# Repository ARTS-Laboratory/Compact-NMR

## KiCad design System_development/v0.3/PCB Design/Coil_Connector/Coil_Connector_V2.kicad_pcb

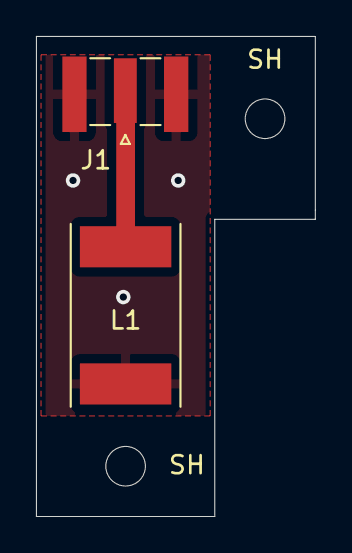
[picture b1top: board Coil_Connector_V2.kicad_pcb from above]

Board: 2 copper layers, 15.5 x 26.7 mm, 4 parts (0 on the bottom side), 2 nets.

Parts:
J1: Conn_Coaxial; SMA_Samtec_SMA-J-P-X-ST-EM1_EdgeMount
L1: L; L_Coil
SH: MountingHole_2.2mm_M2
SH#2: MountingHole_2.2mm_M2

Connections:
GND: J1.2, L1.2
unnamed: J1.1, L1.1

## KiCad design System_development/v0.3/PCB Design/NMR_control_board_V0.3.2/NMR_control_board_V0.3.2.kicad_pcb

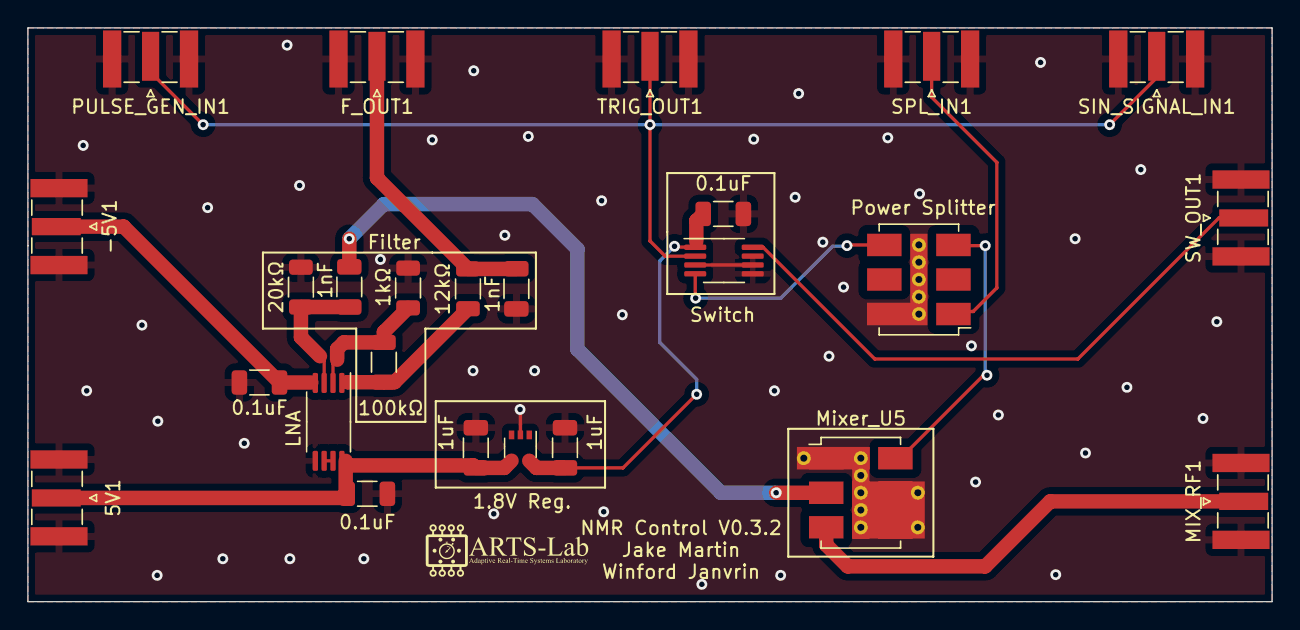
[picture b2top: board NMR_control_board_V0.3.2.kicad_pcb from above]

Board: 2 copper layers, 91.4 x 42.2 mm, 25 parts (0 on the bottom side), 16 nets.

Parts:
1.8V Reg.: NCP715-1.8V; SOT-353_SC-70-5
1kΩ, 12kΩ, 20kΩ, 100kΩ: R; R_1206_3216Metric
1nF, 1nF#2: C; C_1206_3216Metric
5V1: Conn_Coaxial; SMA_Samtec_SMA-J-P-X-ST-EM1_EdgeMount
-5V1: Conn_Coaxial; SMA_Samtec_SMA-J-P-X-ST-EM1_EdgeMount
C2, C4: 1uF; C_1206_3216Metric
C5, C6, C7: 0.1uF; C_1206_3216Metric
F_OUT1: Conn_Coaxial; SMA_Samtec_SMA-J-P-X-ST-EM1_EdgeMount
LNA: LM4565; TSSOP-8_4.4x3mm_P0.65mm
MIX_RF1: Conn_Coaxial; SMA_Samtec_SMA-J-P-X-ST-EM1_EdgeMount
Mixer_U5: ADE-6; Mini-Circuits_CD542_LandPatternPL-052
PULSE_GEN_IN1: Conn_Coaxial; SMA_Samtec_SMA-J-P-X-ST-EM1_EdgeMount
Power Splitter: ADP-2-1W; Mini-Circuits_CD636_LandPatternPL-035
SIN_SIGNAL_IN1: Conn_Coaxial; SMA_Samtec_SMA-J-P-X-ST-EM1_EdgeMount
SPL_IN1: Conn_Coaxial; SMA_Samtec_SMA-J-P-X-ST-EM1_EdgeMount
SW_OUT1: Conn_Coaxial; SMA_Samtec_SMA-J-P-X-ST-EM1_EdgeMount
Switch: ADG901BRMZ; MSOP-8_3x3mm_P0.65mm
TRIG_OUT1: Conn_Coaxial; SMA_Samtec_SMA-J-P-X-ST-EM1_EdgeMount

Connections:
GND: 1.8V Reg..2 (GND), 1kΩ.1, 1nF#2.1, 5V1.2 (Ext), 20kΩ.2, -5V1.2 (Ext), C2.2, C4.2, C5.1, C6.1, C7.1, F_OUT1.2 (Ext), LNA.5 (+IN2), MIX_RF1.2 (Ext), Mixer_U5.1 (GND), Mixer_U5.4 (GND), Mixer_U5.5 (GND), PULSE_GEN_IN1.2 (Ext), Power Splitter.6 (GND), SIN_SIGNAL_IN1.2 (Ext), SPL_IN1.2 (Ext), SW_OUT1.2 (Ext), Switch.3 (GND), Switch.5 (GND), Switch.6 (GND), Switch.7 (GND), TRIG_OUT1.2 (Ext)
unnamed: 1.8V Reg..4 (IN), 5V1.1 (In), C2.1, C7.2, LNA.8 (VCC)
unnamed: -5V1.1 (In), C6.2, LNA.4 (VEE)
unnamed: 1nF.1, 20kΩ.1, LNA.3 (+IN1)
unnamed: 1nF.2, Mixer_U5.2 (IF)
unnamed: 1nF#2.2, 12kΩ.2, F_OUT1.1 (In)
unnamed: 1.8V Reg..5 (OUT), C4.1, C5.2, Switch.1 (VDD)
unnamed: MIX_RF1.1 (In), Mixer_U5.3 (RF)
unnamed: 1kΩ.2, 100kΩ.1, LNA.2 (-IN1)
unnamed: 12kΩ.1, 100kΩ.2, LNA.1 (OUT1)
unnamed: Power Splitter.1 (SUM), SPL_IN1.1 (In)
unnamed: SW_OUT1.1 (In), Switch.8 (RF2)
unnamed: LNA.6 (-IN2), LNA.7 (OUT2)
unnamed: Mixer_U5.6 (LO), Power Splitter.3 (PORT1)
unnamed: Power Splitter.4 (PORT2), Switch.4 (RF1)
unnamed: PULSE_GEN_IN1.1 (In), SIN_SIGNAL_IN1.1 (In), Switch.2 (CTRL), TRIG_OUT1.1 (In)

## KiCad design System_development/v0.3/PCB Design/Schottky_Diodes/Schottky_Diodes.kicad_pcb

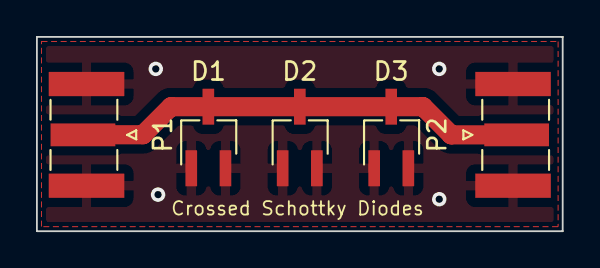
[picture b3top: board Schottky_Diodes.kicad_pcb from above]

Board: 2 copper layers, 29.2 x 10.8 mm, 5 parts (0 on the bottom side), 2 nets.

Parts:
D1, D2, D3: D_Schottky_Dual_Series_AKC; TSOT-23_HandSoldering
P1, P2: Conn_Coaxial; SMA_Samtec_SMA-J-P-X-ST-EM1_EdgeMount

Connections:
GND: D1.1 (A), D1.2 (K), D2.1 (A), D2.2 (K), D3.1 (A), D3.2 (K), P1.2 (Ext), P2.2 (Ext)
unnamed: D1.3 (common), D2.3 (common), D3.D3 (common), P1.1 (In), P2.1 (In)

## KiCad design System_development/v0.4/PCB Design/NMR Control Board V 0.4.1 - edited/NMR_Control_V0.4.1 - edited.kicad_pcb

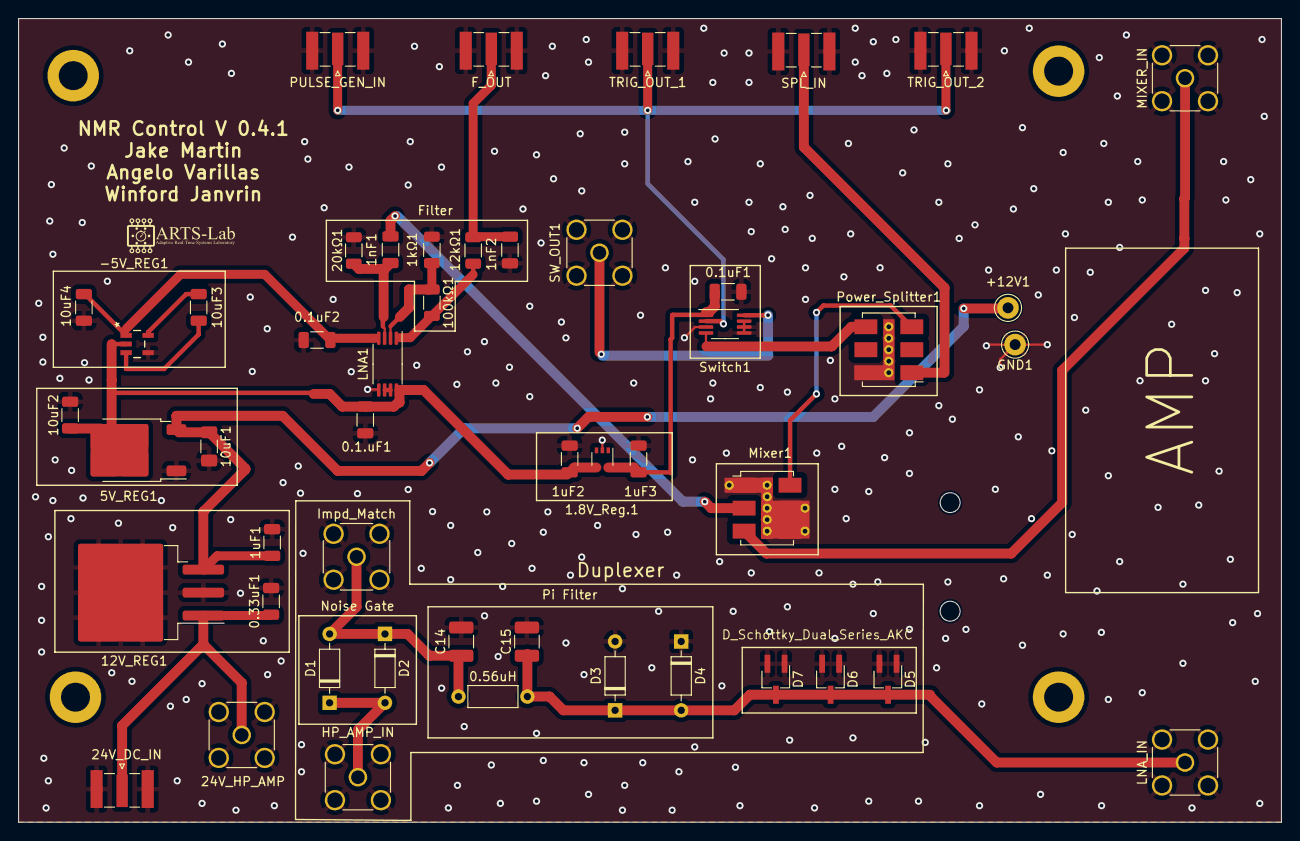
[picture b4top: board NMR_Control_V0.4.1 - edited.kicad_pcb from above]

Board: 2 copper layers, 139.7 x 88.9 mm, 49 parts (0 on the bottom side), 23 nets.

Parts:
0.1.uF1, 0.1uF2: 0.1uF; C_1206_3216Metric
0.1uF1: 0.1 uF; C_1206_3216Metric
0.33uF1: 0.33 uF; C_1206_3216Metric
0.56uH: L; L_Axial_L5.3mm_D2.2mm_P7.62mm_Horizontal_Vishay_IM-1
1.8V_Reg.1: NCP715-1.8V; SOT-353_SC-70-5
1kΩ1, 12kΩ1, 20kΩ1, 100kΩ1: R; R_1206_3216Metric
1nF1, 1nF2: C; C_1206_3216Metric
1uF1, 1uF2, 1uF3: 1 uF; C_1206_3216Metric
5V_REG1: NCP1117-5.0_TO252; TO-252-2
10uF1: 10 uF; C_1206_3216Metric_Pad1.33x1.80mm_HandSolder
10uF2, 10uF3, 10uF4: 10 uF; C_1206_3216Metric
12V_REG1: LM7812_TO220; TO-263-3_TabPin2
24V_DC_IN: Conn_Coaxial; SMA_Samtec_SMA-J-P-X-ST-EM1_EdgeMount
24V_HP_AMP: Conn_Coaxial; SMA_Amphenol_132291_Vertical
+12V1: Pin Hole; Pin_D1.0mm_L10.0mm_LooseFit
-5V_REG1: LM828M5; MF05A
C14, C15: C; C_1210_3225Metric_Pad1.33x2.70mm_HandSolder
D1, D2, D3, D4: 1N4148; D_DO-35_SOD27_P7.62mm_Horizontal
D5, D6, D7: D_Schottky_Dual_Series_AKC; TSOT-23_HandSoldering
F_OUT: Conn_Coaxial; SMA_Samtec_SMA-J-P-X-ST-EM1_EdgeMount
GND1: Pin Hole; Pin_D1.0mm_L10.0mm_LooseFit
HP_AMP_IN: Conn_Coaxial; SMA_Amphenol_132291_Vertical
Impd_Match: Conn_Coaxial; SMA_Amphenol_132134_Vertical
LNA1: LM4565; TSSOP-8_4.4x3mm_P0.65mm
LNA_IN: Conn_Coaxial; SMA_Amphenol_132291_Vertical
MIXER_IN: Conn_Coaxial; SMA_Amphenol_132291_Vertical
Mixer1: ADE-6; Mini-Circuits_CD542_LandPatternPL-052
PULSE_GEN_IN: Conn_Coaxial; SMA_Samtec_SMA-J-P-X-ST-EM1_EdgeMount
Power_Splitter1: ADP-2-1W; Mini-Circuits_CD636_LandPatternPL-035
SPL_IN: Conn_Coaxial; SMA_Samtec_SMA-J-P-X-ST-EM1_EdgeMount
SW_OUT1: Conn_Coaxial; SMA_Amphenol_132291_Vertical
Switch1: ADG901BRMZ; MSOP-8_3x3mm_P0.65mm
TRIG_OUT_1, TRIG_OUT_2: Conn_Coaxial; SMA_Samtec_SMA-J-P-X-ST-EM1_EdgeMount

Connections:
GND: 0.1.uF1.1, 0.1uF1.1, 0.1uF2.1, 0.33uF1.2, 1.8V_Reg.1.2 (GND), 1kΩ1.1, 1nF2.1, 1uF1.2, 1uF2.2, 1uF3.2, 5V_REG1.1 (GND), 10uF1.2, 10uF2.2, 10uF4.2, 12V_REG1.2 (GND), 20kΩ1.2, 24V_DC_IN.2 (Ext), 24V_HP_AMP.2 (Ext), -5V_REG1.4 (GND), C14.2, C15.2, D3.2 (A), D4.1 (K), D5.1 (A), D5.2 (K), D6.1 (A), D6.2 (K), D7.1 (A), D7.2 (K), F_OUT.2 (Ext), GND1.1 (In), HP_AMP_IN.2 (Ext), Impd_Match.2 (Ext), LNA1.5 (+IN2), LNA_IN.2 (Ext), MIXER_IN.2 (Ext), Mixer1.1 (GND), Mixer1.4 (GND), Mixer1.5 (GND), PULSE_GEN_IN.2 (Ext), Power_Splitter1.6 (GND), SPL_IN.2 (Ext), SW_OUT1.2 (Ext), Switch1.3 (GND), Switch1.5 (GND), Switch1.6 (GND), Switch1.7 (GND), TRIG_OUT_1.2 (Ext), TRIG_OUT_2.2 (Ext)
unnamed: 0.1uF1.2, 1.8V_Reg.1.5 (OUT), 1uF3.1, Switch1.1 (VDD)
unnamed: 0.33uF1.1, 12V_REG1.1 (VI), 24V_DC_IN.1 (In), 24V_HP_AMP.1 (In)
unnamed: 1uF1.1, 5V_REG1.3 (VI), 10uF1.1, 12V_REG1.3 (VO), +12V1.1 (In)
unnamed: 10uF3.1, -5V_REG1.5 (C1+)
unnamed: 10uF3.2, -5V_REG1.3 (C1-)
unnamed: 0.1uF2.2, 10uF4.1, -5V_REG1.1 (OUT), LNA1.4 (VEE)
unnamed: 0.1.uF1.2, 1.8V_Reg.1.4 (IN), 1uF2.1, 5V_REG1.2 (VO), 10uF2.1, -5V_REG1.2 (V+), LNA1.8 (VCC)
unnamed: 0.56uH.1, C14.1, D1.2 (A), D2.1 (K), Impd_Match.1 (In)
unnamed: D1.1 (K), D2.2 (A), HP_AMP_IN.1 (In)
unnamed: 0.56uH.2, C15.1, D3.1 (K), D4.2 (A), D5.3 (common), D6.3 (common), D7.3 (common), LNA_IN.1 (In)
unnamed: 1nF2.2, 12kΩ1.2, F_OUT.1 (In)
unnamed: 1nF1.1, 20kΩ1.1, LNA1.3 (+IN1)
unnamed: 1kΩ1.2, 100kΩ1.1, LNA1.2 (-IN1)
unnamed: LNA1.6 (-IN2), LNA1.7 (OUT2)
unnamed: 12kΩ1.1, 100kΩ1.2, LNA1.1 (OUT1)
unnamed: MIXER_IN.1 (In), Mixer1.3 (RF)
unnamed: 1nF1.2, Mixer1.2 (IF)
unnamed: Mixer1.6 (LO), Power_Splitter1.3 (PORT1)
unnamed: PULSE_GEN_IN.1 (In), Switch1.2 (CTRL), TRIG_OUT_1.1 (In), TRIG_OUT_2.1 (In)
unnamed: Power_Splitter1.4 (PORT2), Switch1.4 (RF1)
unnamed: Power_Splitter1.1 (SUM), SPL_IN.1 (In)
unnamed: SW_OUT1.1 (In), Switch1.8 (RF2)

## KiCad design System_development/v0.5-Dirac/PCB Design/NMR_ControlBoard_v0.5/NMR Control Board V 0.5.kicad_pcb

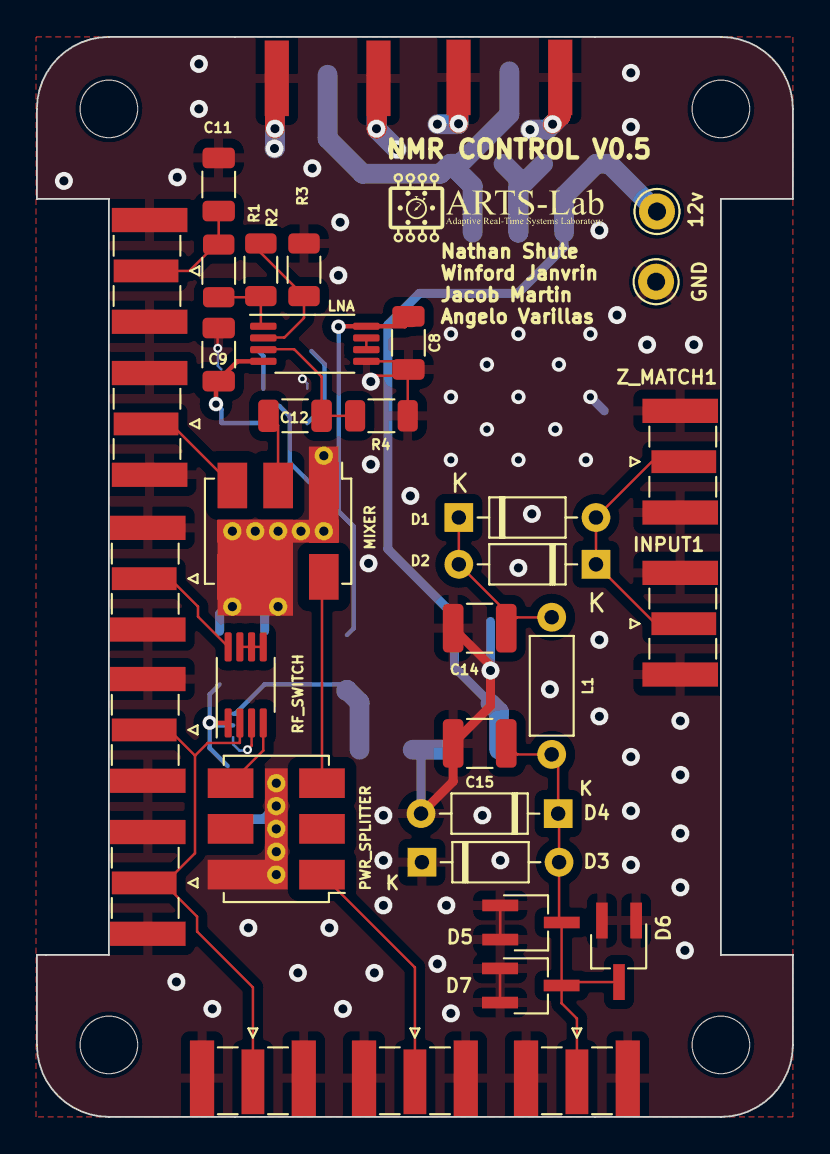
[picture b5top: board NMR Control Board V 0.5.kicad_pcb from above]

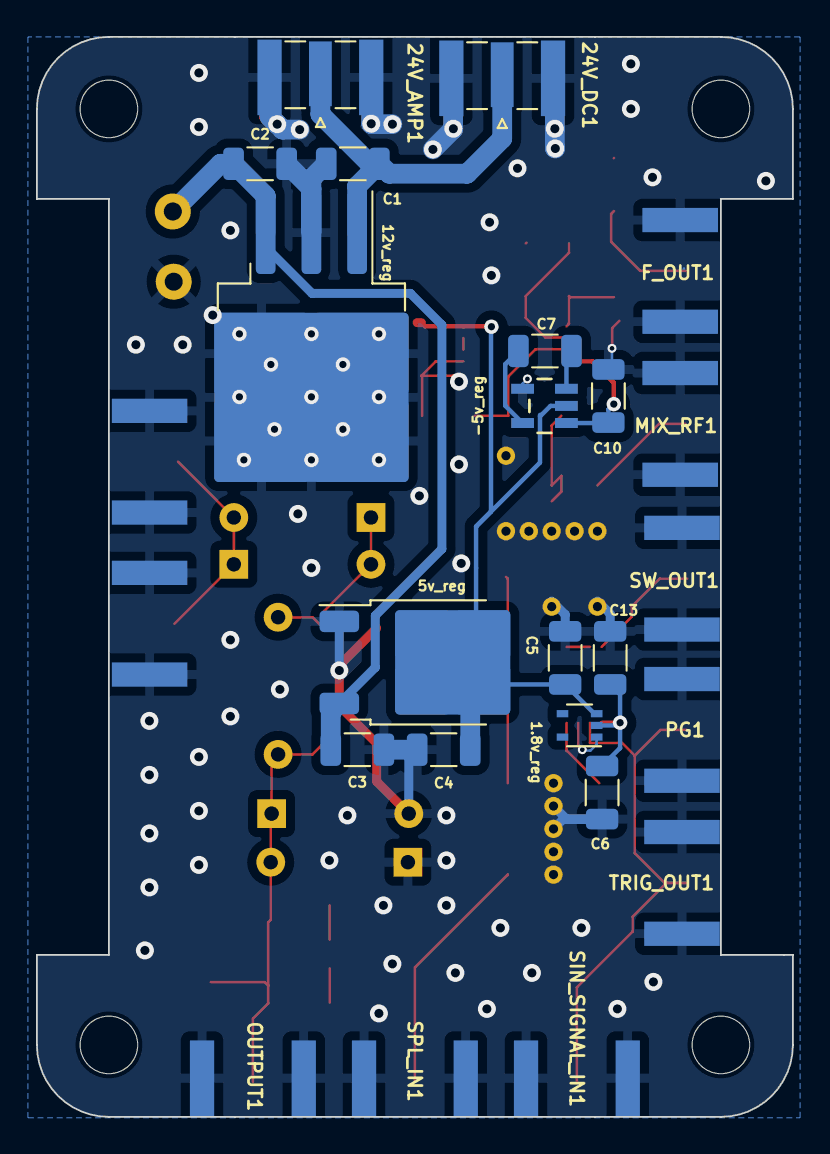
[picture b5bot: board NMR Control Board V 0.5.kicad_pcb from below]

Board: 4 copper layers, 42.0 x 60.0 mm, 53 parts (15 on the bottom side), 24 nets.

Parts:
1.8v_reg: NCP715-1.8v; SOT-353_SC-70-5
5v_reg: NCP1117-5.0_TO252; TO-252-2
12v: MountingHole_Pad; Pin_D1.0mm_L10.0mm
12v_reg: LM7812_TO220; TO-263-3_TabPin2
24V_AMP1: 24V_AMP1; SMA_Samtec_SMA-J-P-X-ST-EM1_EdgeMount
24V_DC1: 24V_DC1; SMA_Samtec_SMA-J-P-X-ST-EM1_EdgeMount
-5v_reg: LM828(-5v); MF05A
C1: .33uF; C_1206_3216Metric
C2, C5, C6: 1uF; C_1206_3216Metric
C3, C4, C7, C10: 10uF; C_1206_3216Metric
C8, C9, C13: 0.1uF; C_1206_3216Metric
C11, C12: 1nF; C_1206_3216Metric
C14, C15: C; C_1210_3225Metric
D1, D2: D; D_DO-35_SOD27_P7.62mm_Horizontal
D3, D4: 1N4148; D_DO-35_SOD27_P7.62mm_Horizontal
D5, D6, D7: D_Dual_Series_AKC; TSOT-23_HandSoldering
F_OUT1: F_OUT1; SMA_Samtec_SMA-J-P-X-ST-EM1_EdgeMount
GND: MountingHole_Pad; Pin_D1.0mm_L10.0mm
H3, H4, H5, H6: MountingHole; MountingHole_3.2mm_M3
INPUT1: INPUT1; SMA_Samtec_SMA-J-P-X-ST-EM1_EdgeMount
L1: 0.56uH; L_Axial_L5.3mm_D2.2mm_P7.62mm_Horizontal_Vishay_IM-1
LNA: LM4565FV_J-GE2; TSSOP-8_4.4x3mm_P0.65mm
MIXER: ADE-6; Mini-Circuits_CD542_LandPatternPL-052
MIX_RF1: MIX_RF1; SMA_Samtec_SMA-J-P-X-ST-EM1_EdgeMount
OUTPUT1: OUTPUT1; SMA_Samtec_SMA-J-P-X-ST-EM1_EdgeMount
PG1: PULSE_GEN_IN1; SMA_Samtec_SMA-J-P-X-ST-EM1_EdgeMount
PWR_SPLITTER: ADP-2-1W; Mini-Circuits_CD636_LandPatternPL-035
R1: 12k; R_1206_3216Metric
R2: 100k; R_1206_3216Metric
R3: 1k; R_1206_3216Metric
R4: 20k; R_1206_3216Metric
RF_SWITCH: ADG901BRMZ; MSOP-8_3x3mm_P0.65mm
SIN_SIGNAL_IN1: SIN_SIGNAL_IN1; SMA_Samtec_SMA-J-P-X-ST-EM1_EdgeMount
SPL_IN1: SPL_IN1; SMA_Samtec_SMA-J-P-X-ST-EM1_EdgeMount
SW_OUT1: SW_OUT1; SMA_Samtec_SMA-J-P-X-ST-EM1_EdgeMount
TRIG_OUT1: TRIG_OUT1; SMA_Samtec_SMA-J-P-X-ST-EM1_EdgeMount
Z_MATCH1: Z_MATCH1; SMA_Samtec_SMA-J-P-X-ST-EM1_EdgeMount

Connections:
1.8v: 1.8v_reg.2 (VO), C6.1, C13.2, RF_SWITCH.1 (VDD)
5v: 1.8v_reg.3 (VI), 5v_reg.2 (VO), -5v_reg.2 (V+), C4.1, C5.1, C8.1, LNA.8 (VCC)
12v: 5v_reg.3 (VI), 12v.1, 12v_reg.3 (VO), C2.1, C3.1
24v: 12v_reg.1 (VI), 24V_AMP1.1 (In), 24V_DC1.1 (In), C1.1
-5v: -5v_reg.1 (OUT), C9.1, C10.1, LNA.4 (VEE)
GND: 1.8v_reg.1 (GND), 5v_reg.1 (GND), 12v_reg.2 (GND), 24V_AMP1.2 (Ext), 24V_DC1.2 (Ext), -5v_reg.4 (GND), C1.2, C2.2, C3.2, C4.2, C5.2, C6.2, C8.2, C9.2, C10.2, C11.2, C13.1, C14.2, C15.2, D3.1 (K), D4.2 (A), D5.1 (A), D5.2 (K), D6.1 (A), D6.2 (K), D7.1 (A), D7.2 (K), F_OUT1.2 (Ext), GND.1, INPUT1.2 (Ext), LNA.5 (+IN2), MIXER.1 (GND), MIXER.4 (GND), MIXER.5 (GND), MIX_RF1.2 (Ext), OUTPUT1.2 (Ext), PG1.2 (Ext), PWR_SPLITTER.6 (GND), R3.1, R4.2, RF_SWITCH.3 (GND), SIN_SIGNAL_IN1.2 (Ext), SPL_IN1.2 (Ext), SW_OUT1.2 (Ext), TRIG_OUT1.2 (Ext), Z_MATCH1.2 (Ext)
IF: C12.2, MIXER.2 (IF)
unnamed: D1.2 (A), D2.1 (K), INPUT1.1 (In), Z_MATCH1.1 (In)
unnamed: C14.1, D1.1 (K), D2.2 (A), L1.1
unnamed: C15.1, D3.2 (A), D4.1 (K), D5.3 (common), D6.3 (common), D7.3 (common), L1.2, OUTPUT1.1 (In)
unnamed: C11.1, F_OUT1.1 (In), R1.2
unnamed: MIXER.3 (RF), MIX_RF1.1 (In)
unnamed: PWR_SPLITTER.1 (SUM), SPL_IN1.1 (In)
unnamed: RF_SWITCH.5 (GND), RF_SWITCH.6 (GND), RF_SWITCH.7 (GND)
unnamed: PG1.1 (In), RF_SWITCH.2 (CTRL), SIN_SIGNAL_IN1.1 (In), TRIG_OUT1.1 (In)
unnamed: RF_SWITCH.8 (RF2), SW_OUT1.1 (In)
unnamed: -5v_reg.5 (C+), C7.1
unnamed: -5v_reg.3 (C-), C7.2
unnamed: C12.1, LNA.3 (+IN1), R4.1
unnamed: LNA.2 (-IN1), R2.1, R3.2
unnamed: LNA.6 (-IN2), LNA.7 (OUT2)
unnamed: LNA.1 (OUT1), R1.1, R2.2
unnamed: MIXER.6 (LO), PWR_SPLITTER.3 (PORT1)
unnamed: PWR_SPLITTER.4 (PORT2), RF_SWITCH.4 (RF1)

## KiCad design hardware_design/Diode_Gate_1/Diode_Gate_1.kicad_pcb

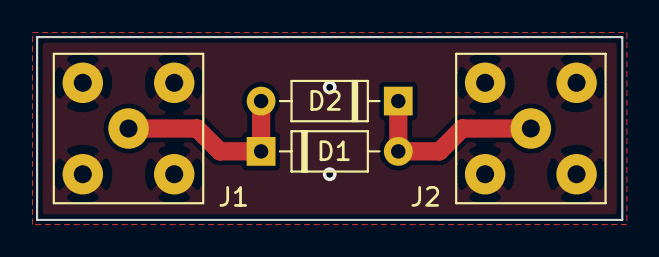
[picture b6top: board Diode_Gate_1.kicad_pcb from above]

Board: 2 copper layers, 32.5 x 10.2 mm, 4 parts (0 on the bottom side), 3 nets.

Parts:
D1, D2: 1N4148; D_DO-35_SOD27_P7.62mm_Horizontal
J1, J2: Conn_Coaxial; SMA_Amphenol_132203-12_Horizontal

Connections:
GND: J1.2, J2.2
unnamed: D1.1, D2.2, J1.1
unnamed: D1.2, D2.1, J2.1

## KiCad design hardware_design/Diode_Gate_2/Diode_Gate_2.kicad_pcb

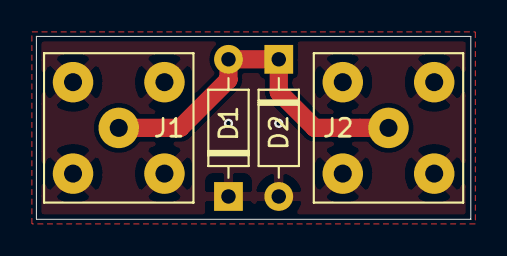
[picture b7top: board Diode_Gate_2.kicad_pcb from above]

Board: 2 copper layers, 24.1 x 10.2 mm, 4 parts (0 on the bottom side), 2 nets.

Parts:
D1, D2: 1N4148; D_DO-35_SOD27_P7.62mm_Horizontal
J1, J2: Conn_Coaxial; SMA_Amphenol_132203-12_Horizontal

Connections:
GND: D1.1, D2.2, J1.2, J2.2
unnamed: D1.2, D2.1, J1.1, J2.1
